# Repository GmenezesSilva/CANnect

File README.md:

# CANnect

Adaptador USB–CAN baseado no **ESP32-S3**, com firmware desenvolvido sobre o
ESP-IDF. O dispositivo recebe e transmite quadros CAN pela USB usando o
protocolo SLCAN, permitindo sua integração com ferramentas compatíveis, como o
[`python-can`](https://python-can.readthedocs.io/).

## Recursos

- Interface USB CDC implementada com TinyUSB.
- Comunicação CAN pelo periférico TWAI do ESP32-S3.
- Quadros CAN clássicos com identificadores padrão (11 bits) e estendidos
  (29 bits), com até 8 bytes de dados.
- Comandos SLCAN para abrir e fechar o canal, configurar a taxa de transmissão
  e enviar quadros.
- Componentes separados para o adaptador CAN, a interface USB e o parser SLCAN.

O firmware **não implementa CAN FD nem telemetria Wi-Fi**. A taxa CAN inicial é
de 500 kbit/s; o protocolo SLCAN também oferece estas opções: 10, 20, 50, 100,
125, 250, 500 e 800 kbit/s, além de 1 Mbit/s.

## Estrutura do repositório

```text
.
├── firmware/
│   ├── CANnect/             # Projeto ESP-IDF
│   │   ├── main/            # Inicialização e configuração do firmware
│   │   └── components/
│   │       ├── can_adapter/
│   │       ├── slcan_parser/
│   │       └── usb_adapter/
│   └── LICENSE              # Licença do firmware
└── Hardware/
    ├── CANnect/             # Projeto da placa no KiCad
    └── LICENSE              # Licença do hardware
```

## Requisitos

- ESP-IDF instalado e ambiente de desenvolvimento ativado, com suporte ao
  ESP32-S3 e ao driver TWAI On-Chip utilizado pelo projeto.
- Placa CANnect ou hardware compatível com ESP32-S3 e transceptor CAN externo.
- Cabo USB de dados.

As dependências do firmware são declaradas em
[`firmware/CANnect/main/idf_component.yml`](firmware/CANnect/main/idf_component.yml)
e são gerenciadas pelo ESP-IDF Component Manager.

## Compilar e gravar

Na raiz do repositório, com o ambiente do ESP-IDF ativado:

```bash
cd firmware/CANnect
idf.py set-target esp32s3
idf.py menuconfig
```

No menu `CANnect`, configure `CAN TX GPIO` e `CAN RX GPIO` de acordo com a
placa e com a ligação ao transceptor. Ajuste também `CAN bitrate` se necessário.
Os pinos começam sem configuração válida; o firmware não inicializa enquanto
eles não forem definidos.

Compile e grave a placa:

```bash
idf.py build
idf.py -p PORT flash monitor
```

Substitua `PORT` pela porta serial da placa, por exemplo `/dev/ttyACM0` no Linux
ou `COM3` no Windows. Para apenas compilar, execute `idf.py build`.

## Uso via SLCAN

Depois de gravar o firmware, conecte a porta USB CDC a um aplicativo compatível
com SLCAN. O parser aceita:

| Comando | Função |
| --- | --- |
| `O` | Abre o canal CAN |
| `C` | Fecha o canal CAN |
| `S0`–`S8` | Seleciona a taxa CAN, conforme a tabela abaixo |
| `t` / `T` | Envia quadro com identificador padrão / estendido |
| `V`, `N`, `F` | Consulta versão, número e status do adaptador |

| Comando | Taxa |
| --- | ---: |
| `S0` | 10 kbit/s |
| `S1` | 20 kbit/s |
| `S2` | 50 kbit/s |
| `S3` | 100 kbit/s |
| `S4` | 125 kbit/s |
| `S5` | 250 kbit/s |
| `S6` | 500 kbit/s |
| `S7` | 800 kbit/s |
| `S8` | 1 Mbit/s |

Quadros recebidos no barramento são enviados pela USB em formato SLCAN quando o
canal está aberto. A taxa escolhida também precisa ser suportada pelos demais
dispositivos conectados ao barramento.

## Licenças

- Firmware: [MIT](firmware/LICENSE).
- Hardware: [CERN-OHL-P v2](Hardware/LICENSE).

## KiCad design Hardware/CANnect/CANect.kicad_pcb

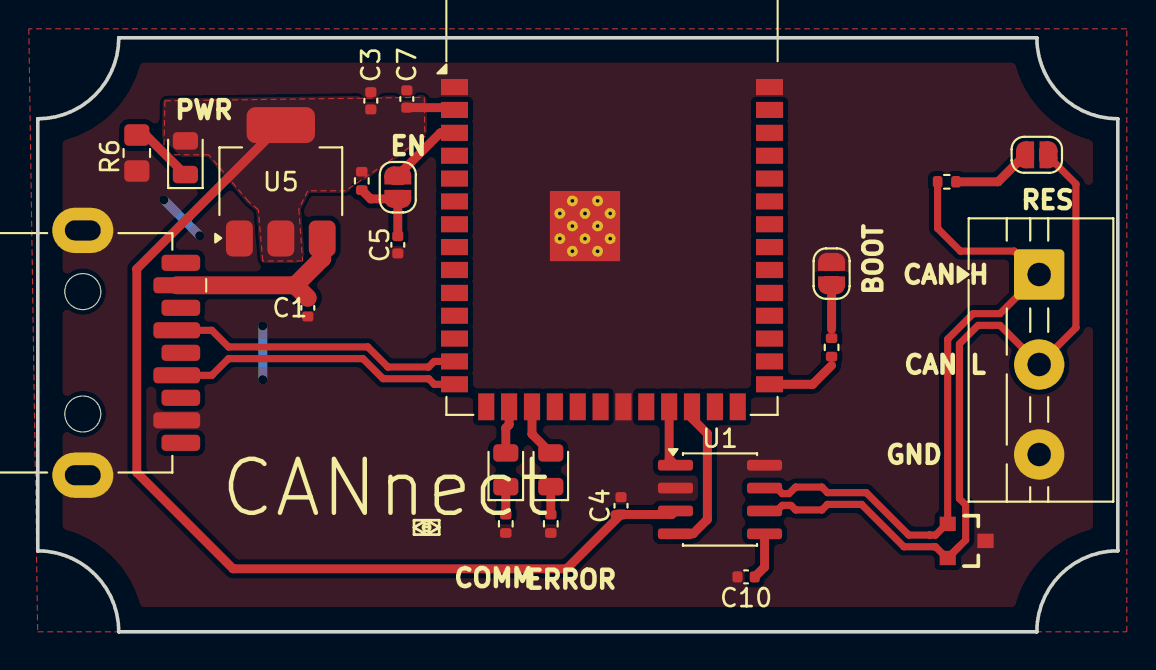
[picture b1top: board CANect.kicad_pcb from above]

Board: 2 copper layers, 60.0 x 33.0 mm, 24 parts (0 on the bottom side), 20 nets.

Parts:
BOOT1: Jumper_2_Open; SolderJumper-2_P1.3mm_Open_RoundedPad1.0x1.5mm
C1: 4.7uF; C_0402_1005Metric
C3, C5: 10uF; C_0402_1005Metric
C4, C7, C10: 100nF; C_0402_1005Metric
CR1: PESD2CAN_215; SOT23-3
ENABLE1: Jumper_2_Open; SolderJumper-2_P1.3mm_Open_RoundedPad1.0x1.5mm
J2: USB3_A; USB3_A_Receptacle_Wuerth_692122030100
J4: Screw_Terminal_01x03; TerminalBlock_MaiXu_MX126-5.0-03P_1x03_P5.00mm
JP1: Jumper_2_Open; SolderJumper-2_P1.3mm_Open_RoundedPad1.0x1.5mm
LD1: VERM; LED_0805_2012Metric
LD2: GREEN; LED_0805_2012Metric
LD3: RED; LED_0805_2012Metric
R3, R7, R8: 120; R_0402_1005Metric
R4, R5: 120R; R_0402_1005Metric
R6: 120; R_0805_2012Metric_Pad1.20x1.40mm_HandSolder
U1: SN65HVD230; SOIC-8_3.9x4.9mm_P1.27mm
U2: ESP32-S3-WROOM-1
U5: AMS1117-3.3; SOT-223-3_TabPin2

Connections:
+3V3: C3.1, C4.1, C7.1, LD1.2 (A), R4.1, U1.3 (VCC), U2.2 (3V3), U5.2 (VO)
+5V: C1.1, J2.1 (VBUS), U5.3 (VI)
/BT_BOOT: R5.1, U2.27 (IO0)
/BT_EN: ENABLE1.2 (B), U2.3 (EN)
/CAN+: CR1.1 (CATHODE), J4.1, R3.1, U1.7 (CANH)
/CAN-: CR1.2 (CATHODE), J4.2, JP1.1 (A), U1.6 (CANL)
/CAN_RX-: U1.4 (R), U2.24 (IO47)
/CAN_TX+: U1.1 (D), U2.23 (IO21)
/COMM: LD2.2 (A), U2.16 (IO46)
/ERROR: LD3.2 (A), U2.17 (IO9)
/USB_DN: J2.2 (D-), U2.13 (USB_D-)
/USB_DP: J2.3 (D+), U2.14 (USB_D+)
GND: BOOT1.2 (B), C1.2, C3.2, C4.2, C5.2, C7.2, C10.2, CR1.3 (COMMONCATHODE), J2.4 (GND), J2.SH (SHIELD), J4.3, R6.1, R7.1, R8.1, U1.2 (GND), U1.8 (Rs), U2.1 (GND), U2.21 (IO13), U2.40 (GND), U2.41 (GND), U5.1 (GND)
unnamed: BOOT1.1 (A), R5.2
unnamed: C5.1, ENABLE1.1 (A), R4.2
unnamed: JP1.2 (B), R3.2
unnamed: LD1.1 (K), R6.2
unnamed: LD2.1 (K), R7.2
unnamed: LD3.1 (K), R8.2
unnamed: C10.1, U1.5 (Vref)

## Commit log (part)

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2026-06-11 chore: initial monorepo structure with completed V0 USB-CAN hardware routing
2026-06-14 feat(core): initial project structure and license files
2026-06-14 chore: setup project README
2026-06-18 feat(usb): implement base CDC adapter architecture with echo test
2026-06-22 test(usb): implement event-driven rx/tx tasks with echo dataflow to validate TinyUSB
2026-06-25 feat(usb): reduce declared queues to simplify the process after the echo test
